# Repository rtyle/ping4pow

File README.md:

# ping4pow

## Motivation

Upon network recovery,
sensitive equipment may need to be rebooted after things have settled.
Some equipment may need to be rebooted to facilitate network recovery.
For many such equipment, power to the device can be cycled to achieve this.
Without automation, this must be done manually.
It would be better with automation that could recognize such conditions and cycle power.

There are commercially available/configurable devices that address this issue.

* [WattBox](https://www.snapav.com/shop/en/snapav/wattbox)
* [Ping Watchdog](https://www.netio-products.com/en/glossary/watchdog-ping-ip-watchdog)

This is a better solution.

Ping4pow can only switch loads that can be safely handled by its relay.
Relay solutions that are embedded in its small footprint will only be able to switch low voltage loads.
However, an external relay solution (like an [iot-power-relay](https://dlidirect.com/products/iot-power-relay))
can be controlled by a GPIO pin for more demanding loads.

## Features

* Small, attractive package
* Display with touchscreen user interface
* Display can be turned off
* User interface can be locked
* Home Assistant integrable but not required for automation
* Wired (ethernet) access for reliable network monitoring
* Powered by [Power-over-Ethernet](https://en.wikipedia.org/wiki/Power_over_Ethernet) (PoE)
* Flexible relay solutions for handling loads
* Galvanically isolated switching of equipment power
* Network health is determined by [ping](https://en.wikipedia.org/wiki/Ping_(networking_utility))ing multiple IP addresses
* Network failure is when all addresses can not be pinged for a while.
* Network recovery may be facilitated by cycling power; otherwise
* Network recovery is when all addresses can be pinged for a while and then power is cycled.
* Email notification of power cycle.

## Architecture

### Hardware

[M5Stack](https://docs.m5stack.com/en/start/intro/intro) products are used to provide a small and attractive hardware solution
that does not require a custom enclosure for switching low voltage loads.
Our stack needs a core with support from a base LAN PoE module.

* [CoreS3-SE](https://docs.m5stack.com/en/core/M5CoreS3%20SE)
* [Base LAN PoE v1.2](https://docs.m5stack.com/en/base/lan_poe_v12)

To support both the core display and the ethernet LAN at the same time, a custom M5-Bus adapter must be used to resolve GPIO pin conflicts. This might be done using an M5Bus bodge-wired Module Proto. Alternately, the PCB of the Module Proto might be swapped out with one that has the bodge baked in (see [adapter](kicad/projects/adapter)).

* [Module Proto](https://docs.m5stack.com/en/module/proto)

To switch the load we will need a relay. M5Stack provides a 4Relay Module. Alternately, the M5-Bus adapter might be expanded to provide a relay using the frame of an M5Stack Module13.2 Proto (see [adapter_relay](kicad/projects/adapter_relay)).

* [Module13.2 4Relay v1.1](https://docs.m5stack.com/en/module/4Relay%20Module%2013.2_V1.1)
* [Module13.2 Proto](https://docs.m5stack.com/en/module/proto13.2)

A Module13.2 Proto might also be used to bodge-wire the M5-Bus adapter and provide external access to the same GPIO pin used by the adapter_relay.
This could be used to drive an external relay for more demanding loads.

### Software

[ESPHome](https://esphome.io/) is used because of its ability to support our chosen hardware and the potential for other choices.
It can be configured in a high level language (YAML) and will only do what you tell it to do.
A configured device can perform all the automations without any external support.
Optionally, such a device can be used by Home Assistant.

## Deployment

### Hardware

The stack should be assembled with the core on top, followed by the relay solution, the adapter solution and finally the PoE base.

#### Module13.2 4Relay v1.1 and Module Proto adapter

This solution uses the Module13.2 4Relay v1.1 and a separate M5-Bus Module Proto based adapter. The adapter can be built from the [adapter](kicad/projects/adapter) kicad project or hand made using its schematic for a reference. If hand made, the disconnected male pins should be clipped and the re-routing of signals made using bodge wires.

<picture>
    <source media="(prefers-color-scheme: dark)" srcset="README/adapter.schematic.dark.png">
    <source media="(prefers-color-scheme: light)" srcset="README/adapter.schematic.light.png">
    
</picture>

Only the first [signal relay](https://www.amazon.com/gp/product/B0CWCTHCFT) in the module will be used.
It will be configured to provide module input power to relay output power in a Normally Closed (NC) fashion.
We want the relay to operate in a NC fashion so that when power is removed from the stack the relay will be closed
(power to the controlled device will be on).

Module input power must be galvanically isolated from the M5-Bus (stack) HPWR and system GND.
**Remove** the jumpers that connect these.

<picture>
    <source media="(prefers-color-scheme: dark)" srcset="README/relay.hpwr.dark.png">
    <source media="(prefers-color-scheme: light)" srcset="README/relay.hpwr.light.png">
    
</picture>

Set the relay jumpers in the "load" configuration.

<picture>
    <source media="(prefers-color-scheme: dark)" srcset="README/relay.load.dark.png">
    <source media="(prefers-color-scheme: light)" srcset="README/relay.load.light.png">
    
</picture>

The relay is hard-wired on the module in a Normally Open (NO) fashion.
That is, the relay output power is connected by PCB trace to the NO pin on the relay.
Cut this trace and add a bodge wire to connect the relay ouput power with the NC pin on the relay.

<picture>
    <source media="(prefers-color-scheme: dark)" srcset="README/relay.dark.png">
    <source media="(prefers-color-scheme: light)" srcset="README/relay.light.png">
    
</picture>

Wire module input power pins to an adapter pigtail that accepts the plug of the power adapter of the controlled device.
Alternately, cut the plug off the power adapter and wire the adapter directly to the 4relay input power plug.
Wire relay power output pins to an adapter pigtail that provides the power plug expected by the controlled device.
Alternately, cut the plug off the power adapter and wire the plug directly to the 4relay output power plug.

#### Module13.2 Proto adapter_relay

This solution uses a Module13.2 Proto frame with the PCB replaced with one built from the [adapter_relay](kicad/projects/adapter_relay) kicad project. There is no need for a separate M5-Bus adapter.

The adapter_relay uses a double-pole double-throw (DPDT) [signal relay](https://na.industrial.panasonic.com/products/relays-contactors/mechanical-signal-relays/lineup/signal-relays/series/119572/model/119942) to switch both conductors of the galvanically isolated DC load. Jumpers must be installed in the normally-closed (NC) positions. The load is passed through the board using standard 5.5mm x 2.1mm DC barrel connections. Openings in the frame of the Module13.2 Proto must be expanded to accomodate the DC jacks. It doesn't matter which jack is used for which plug.

#### Base LAN PoE v1.2

Stack an M5-Bus adapter on top using one of the methods described above.
Power, and supply network access, over the RJ45 ethernet port.

### Software

These instructions are written for a Fedora Linux platform.
Similar steps may be taken for other Linux, MacOS or Windows platforms.

Get the source from this repository by the appropriate method:

    git clone https://github.com/rtyle/ping4pow.git
    git clone git@github.com:rtyle/ping4pow.git

All commands documented here are executed from this directory.

    cd ping4pow

Install python

    sudo dnf install python

Create a python virtual environment for this project.

    python -m venv .venv

Activate the virtual environment every time you want to use ESPHome within this project.

    source .venv/bin/activate

With your virtual environment activated, install ESPHome using pip:

    pip install esphome

Configure the order, address and name of each host to be ping-monitored.
Each is specifed by an address, name pair in an m4 host macro invocation.
Add a third argument for a host that must be power-cycled when all are not pingable for a while;
otherwise, wait for all hosts to be pingable for a while before power-cycling.

    cp config/hosts{.example,}.m4; vi config/hosts.m4

Optionally, configure (smtp) email notification.

    cp config/smtp{.example,}.m4; vi config/smtp.m4

Configure secrets.yaml.

    cp config/secrets{.example,}.yaml; vi config/secrets.yaml

These secrets will be protected by flash encryption on/by the device.

Choose an ESPHome configuration for
M5Stack Module13.2 4Relay hardware (default) or a GPIO relay.

    (cd config; m4 ping4pow.m4 > ping4pow.yaml)
    (cd config; m4 -DGPIO_RELAY ping4pow.m4 > ping4pow.yaml)

The first firmware flash of this ESPHome configuration
must be done with a USB cable between your computer and the M5Stack CoreS3.
**Do not interrupt this first boot!**

    esphome run config/ping4pow.yaml

Upon the first boot after the first flash,
the secondary boot loader will encrypt the content of the flash in place.
Subsequently, only use ESPHome to flash Over The Air (OTA)
as ESPHome flashing by USB will cause the firmware to be unencrypted
which will upset the first stage bootloader to no end:

    [11:31:08.073]invalid header: 0x487325b7
    ...

To recover from this problem, the device must be flashed properly:

    bin=.esphome/build/ping4pow/.pioenvs/ping4pow
    python -m esptool --chip esp32s3 --port /dev/ttyACM0 write-flash --encrypt 0x0 $bin/firmware.factory.bin

Connect by ethernet to a power-over-ethernet capable port and unplug the USB cable.
Connect the switched load to the relay.

## Usage

Each ping target defined (by address & name) and ordered (#) in the `hosts.m4` file will be periodically pinged.
Each will be represented by a

* `ping # (address name)` switch (where # is its order) to enable/disable pinging and summary consideration of the target.
* `ping # able` binary sensor that reflects the pingability of the target.
* `ping # since` sensor that reflects the time elapsed since the last change in pingability.

These target ping sensors will be summarized by a

* `ping none` binary sensor that is true unless an enabled target is pingable.
* `ping all` binary sensor that is true unless an enabled target is not pingable.
* `ping some` binary sensor that is true if "ping none" and "ping all" are false.
* `ping count` sensor that reflects the number of enabled and pingable targets.
* `ping since` sensor that reflects the time elapsed since the last change in target pingability.

The automation provided by ping4pow is implemented as a state machine.
These states are reflected in the user interface as switches.
Only one state/switch can be active/on at a time.
States can be entered through a switch action in the user interface.
These states/switches are:

0. `stop`. When on, the state machine is stopped. Turn off to advance to the next state.
1. wait for `ping none`, then advance to the next state.
2. wait while `ping none`, then advance to the next state; otherwise, the previous state.
3. wait for `ping all`, then advance to the next state.
4. wait while `ping all`, then advance to the next state; otherwise, the previous state.
5. `power cycle`: turn power off, pause, turn power on and then start over.

States 3 and 4 are skipped if there is a host that must be power-cycled when all are not pingable for a while.

If there is 
In addition, ping4pow exposes

* A `power` switch that reflects/controls power to the connected load.
* A `since boot` sensor that reflects the time elapsed since booting the ping4pow device.
* A `since power cycle` sensor that reflects the time elapsed since the power to the load was automatically affected.

All since sensors are in units of seconds.

A web-based user interface at http://ping4pow.local exposes these switches and sensors.

<picture>
    <source media="(prefers-color-scheme: dark)" srcset="README/ping4pow.web.dark.png">
    <source media="(prefers-color-scheme: light)" srcset="README/ping4pow.web.light.png">
    
</picture>

These are also presented locally on the ping4pow device's display.

Under the display are soft buttons on the bezel

* <picture>
        <source media="(prefers-color-scheme: dark)" srcset="README/mdi/chevron-double-left.dark.svg">
        <source media="(prefers-color-scheme: light)" srcset="README/mdi/chevron-double-left.light.svg">
        
    </picture> Decrease display brightness
* <picture>
        <source media="(prefers-color-scheme: dark)" srcset="README/mdi/circle-outline.dark.svg">
        <source media="(prefers-color-scheme: light)" srcset="README/mdi/circle-outline.light.svg">
        
    </picture> Navigate home to state tile
* <picture>
        <source media="(prefers-color-scheme: dark)" srcset="README/mdi/chevron-double-right.dark.svg">
        <source media="(prefers-color-scheme: light)" srcset="README/mdi/chevron-double-right.light.svg">
        
    </picture> Increase display brightness

At the bottom of the display is a user interface lock and tile navigation buttons

* <picture>
        <source media="(prefers-color-scheme: dark)" srcset="README/mdi/arrow-left-bold.dark.svg">
        <source media="(prefers-color-scheme: light)" srcset="README/mdi/arrow-left-bold.light.svg">
        
    </picture> Previous tile in rotation
* <picture>
        <source media="(prefers-color-scheme: dark)" srcset="README/mdi/lock.dark.svg">
        <source media="(prefers-color-scheme: light)" srcset="README/mdi/lock.light.svg">
        
    </picture> User input is locked (<picture>
        <source media="(prefers-color-scheme: dark)" srcset="README/mdi/lock-open.dark.svg">
        <source media="(prefers-color-scheme: light)" srcset="README/mdi/lock-open.light.svg">
        
    </picture> when not)
* <picture>
        <source media="(prefers-color-scheme: dark)" srcset="README/mdi/arrow-right-bold.dark.svg">
        <source media="(prefers-color-scheme: light)" srcset="README/mdi/arrow-right-bold.light.svg">
        
    </picture> Next tile in rotation

The rest of the display is used for the current tile.
Using the next and previous tile controls, one can rotate through them.
The tiles are:

* Splash tile
* State tile
* Since tile
* Target tile (one for each)

### Splash Tile

A ping4pow image is displayed briefly on boot before advancing to the next tile.

### State Tile

The top row of buttons reflect states 1, 2, 3 and 4.

* <picture>
        <source media="(prefers-color-scheme: dark)" srcset="README/mdi/cog-pause.dark.svg">
        <source media="(prefers-color-scheme: light)" srcset="README/mdi/cog-pause.light.svg">
        <picture>
        <source media="(prefers-color-scheme: dark)" srcset="README/mdi/network-off.dark.svg">
        <source media="(prefers-color-scheme: light)" srcset="README/mdi/network-off.light.svg">
        
        </picture>
    </picture> wait for <code>ping none</code>
* <picture>
        <source media="(prefers-color-scheme: dark)" srcset="README/mdi/cog-pause.dark.svg">
        <source media="(prefers-color-scheme: light)" srcset="README/mdi/cog-pause.light.svg">
        <picture>
        <source media="(prefers-color-scheme: dark)" srcset="README/mdi/network-off.dark.svg">
        <source media="(prefers-color-scheme: light)" srcset="README/mdi/network-off.light.svg">
        <picture>
        <source media="(prefers-color-scheme: dark)" srcset="README/mdi/dots-horizontal.dark.svg">
        <source media="(prefers-color-scheme: light)" srcset="README/mdi/dots-horizontal.light.svg">
        
    </picture> wait while <code>ping none</code>
* <picture>
        <source media="(prefers-color-scheme: dark)" srcset="README/mdi/cog-pause.dark.svg">
        <source media="(prefers-color-scheme: light)" srcset="README/mdi/cog-pause.light.svg">
        <picture>
        <source media="(prefers-color-scheme: dark)" srcset="README/mdi/network.dark.svg">
        <source media="(prefers-color-scheme: light)" srcset="README/mdi/network.light.svg">
        
    </picture> wait for <code>ping all</code>
* <picture>
        <source media="(prefers-color-scheme: dark)" srcset="README/mdi/cog-pause.dark.svg">
        <source media="(prefers-color-scheme: light)" srcset="README/mdi/cog-pause.light.svg">
        <picture>
        <source media="(prefers-color-scheme: dark)" srcset="README/mdi/network.dark.svg">
        <source media="(prefers-color-scheme: light)" srcset="README/mdi/network.light.svg">
        <picture>
        <source media="(prefers-color-scheme: dark)" srcset="README/mdi/dots-horizontal.dark.svg">
        <source media="(prefers-color-scheme: light)" srcset="README/mdi/dots-horizontal.light.svg">
        
    </picture> wait while <code>ping all</code>

The middle row of buttons reflect state 0, `power` and state 5

* <picture>
        <source media="(prefers-color-scheme: dark)" srcset="README/mdi/cog.dark.svg">
        <source media="(prefers-color-scheme: light)" srcset="README/mdi/cog.light.svg">
        
    </picture> <code>stop</code> (<picture>
        <source media="(prefers-color-scheme: dark)" srcset="README/mdi/cog-stop.dark.svg">
        <source media="(prefers-color-scheme: light)" srcset="README/mdi/cog-stop.light.svg">
        
    </picture> when stopped)
* <picture>
        <source media="(prefers-color-scheme: dark)" srcset="README/mdi/power.dark.svg">
        <source media="(prefers-color-scheme: light)" srcset="README/mdi/power.light.svg">
        
    </picture> <code>power</code>
* <picture>
        <source media="(prefers-color-scheme: dark)" srcset="README/mdi/power-cycle.dark.svg">
        <source media="(prefers-color-scheme: light)" srcset="README/mdi/power-cycle.light.svg">
        
    </picture> <code>power cycle</code>

The bottom row reflects the summary ping sensors.
At most, one of these will be on.
The label on the widget reflecting state of the `ping some` binary sensor will reflect the `ping count` sensor value regardless.

* <picture>
        <source media="(prefers-color-scheme: dark)" srcset="README/mdi/network-off.dark.svg">
        <source media="(prefers-color-scheme: light)" srcset="README/mdi/network-off.light.svg">
        
    </picture> <code>ping none</code>
* <picture>
        <source media="(prefers-color-scheme: dark)" srcset="README/mdi/pound.dark.svg">
        <source media="(prefers-color-scheme: light)" srcset="README/mdi/pound.light.svg">
        
    </picture> <code>ping some</code> with <code>ping count</code> (#)
* <picture>
        <source media="(prefers-color-scheme: dark)" srcset="README/mdi/network.dark.svg">
        <source media="(prefers-color-scheme: light)" srcset="README/mdi/network.light.svg">
        
    </picture> <code>ping all</code>

### Since Tile

The three rows of this tile reflect times since an event.
This time is formatted as either "N/A" (if there was never such an event) or the number of days, hours, minutes and seconds (D HH:MM:SS) since the event.

* <picture>
        <source media="(prefers-color-scheme: dark)" srcset="README/mdi/check-network.dark.svg">
        <source media="(prefers-color-scheme: light)" srcset="README/mdi/check-network.light.svg">
        
    </picture> <code>ping since</code>
* <picture>
        <source media="(prefers-color-scheme: dark)" srcset="README/mdi/power-cycle.dark.svg">
        <source media="(prefers-color-scheme: light)" srcset="README/mdi/power-cycle.light.svg">
        
    </picture> <code>since power cycle</code>
* <picture>
        <source media="(prefers-color-scheme: dark)" srcset="README/mdi/arrow-up-bold-circle.dark.svg">
        <source media="(prefers-color-scheme: light)" srcset="README/mdi/arrow-up-bold-circle.light.svg">
        
    </picture> <code>since boot</code>

### Target Tile

There is a target tile for each ping target in `hosts.m4`.

The first row of this tile reflects whether the target is enabled and its pingability.

* <picture>
        <source media="(prefers-color-scheme: dark)" srcset="README/mdi/cog.dark.svg">
        <source media="(prefers-color-scheme: light)" srcset="README/mdi/cog.light.svg">
        
    </picture> <code>ping # (address name)</code> enabled (<picture>
        <source media="(prefers-color-scheme: dark)" srcset="README/mdi/cog-stop.dark.svg">
        <source media="(prefers-color-scheme: light)" srcset="README/mdi/cog-stop.light.svg">
        
    </picture> when not)
* <picture>
        <source media="(prefers-color-scheme: dark)" srcset="README/mdi/network.dark.svg">
        <source media="(prefers-color-scheme: light)" srcset="README/mdi/network.light.svg">
         <code>ping # able</code> (<picture>
        <source media="(prefers-color-scheme: dark)" srcset="README/mdi/network-off.dark.svg">
        <source media="(prefers-color-scheme: light)" srcset="README/mdi/network-off.light.svg">
        
        </picture> when not)
    </picture>

The next two rows are for `ping # since` and for identifying the target by address and name.

* <picture>
        <source media="(prefers-color-scheme: dark)" srcset="README/mdi/check-network.dark.svg">
        <source media="(prefers-color-scheme: light)" srcset="README/mdi/check-network.light.svg">
        
    </picture> <code>ping # since</code>
* <picture>
        <source media="(prefers-color-scheme: dark)" srcset="README/mdi/tag.dark.svg">
        <source media="(prefers-color-scheme: light)" srcset="README/mdi/tag.light.svg">
         <code>address</code> <code>name</code>
    </picture>

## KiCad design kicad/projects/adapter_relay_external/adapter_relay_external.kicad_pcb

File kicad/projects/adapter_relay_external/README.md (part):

# GPIO Relay Protection Circuit - Design Documentation

## Overview

This protection circuit provides robust, fail-safe control of an external [DLI IoT Power Relay](https://dlidirect.com/products/iot-power-relay) from an ESP32-based ping4pow device powered by PoE. The circuit is specifically designed to protect the ping4pow hardware from operator errors, including accidental dead shorts and incorrect DC power supply connections (up to 48V).

## Design Philosophy

The circuit follows a **defense-in-depth** strategy with multiple layers of protection:
1. **Galvanic isolation** - Complete electrical isolation between GPIO and external connections
2. **Current limiting** - Series resistance limits fault currents to safe levels
3. **Overvoltage clamping** - Zener diode clamps excessive voltages
4. **Overcurrent protection** - Dual polyfuses interrupt fault conditions
5. **Backfeed prevention** - Schottky diode blocks reverse current flow

Each protection mechanism is **independently validated** to ensure the circuit survives even if one protection layer fails.

## Circuit Architecture

### Schematic Overview

<picture>
    <source media="(prefers-color-scheme: dark)" srcset="README/schematic.dark.png">
    <source media="(prefers-color-scheme: light)" srcset="README/schematic.light.png">
    
</picture>

### Signal Flow

**Normal Operation (GPIO HIGH):**
1. 5V from PoE supply passes through input polyfuse F1
2. Schottky diode D1 drops ~0.25V (at 1mA), preventing backfeed to 5V rail
3. Series resistor R1 (82Ω) limits current
4. Output polyfuse F2 provides additional overcurrent protection
5. Voltage arrives at DC Jack (+) at ~4.67V
6. GPIO HIGH drives optocoupler U1 LED with 10mA
7. U1 phototransistor conducts, connecting DC Jack (-) to GND
8. Relay circuit completes: DC Jack (+) → Relay → DC Jack (-) → U1 → GND
9. Relay receives ~0.95mA at ~4.67V and activates

**Zener D2 monitoring:**
- Connected across DC Jack (+) and DC Jack (-)
- During normal operation: 4.75V < 5.1V threshold, Zener not conducting
- During fault: Clamps voltage between DC Jack (+) and DC Jack (-) to ~5.6V

## Component Selection and Justification

### F1 - Input Polyfuse (Littelfuse 0603L001/60YR)
**Specification:** 10mA hold / 50mA trip, 60V, 0603 package

**Purpose:** Protects the 5V PoE supply rail from overcurrent faults, particularly dead shorts at the DC jack output.

**Selection Rationale:**
- **Hold current (10mA):** Normal relay current is ~0.95mA, giving 10.5x safety margin
- **Trip current (50mA):** Dead short produces 58mA, exceeding trip threshold by 16%
- **Trip time at 58mA:** Approximately 5-30 seconds
- **Component stress during trip:** R1 dissipates 0.28W (56% of 0.5W rating), all components safe
- **60V rating:** Exceeds maximum expected voltage (48V) with 25% margin
- **Availability:** Minimum trip current available from Littelfuse in required voltage rating

**Why this trip point:** This was the lowest trip current available in 0603 SMD package with adequate voltage rating. The 50mA trip provides reliable protection for dead shorts (58mA) while not tripping during normal operation (0.95mA).

### F2 - Output Polyfuse (Littelfuse 0603L008YR)
**Specification:** 80mA hold / 200mA trip, 60V, 0603 package

**Purpose:** Protects R1 and D2 from excessive current when external overvoltage sources (wall adapters) are connected to the DC jack.

**Selection Rationale:**
- **Hold current (80mA):** Provides 84x margin over normal relay current
- **Trip current (200mA):** At 48V fault, current reaches 517mA (2.6x trip threshold), causing F2 to trip within 1-2 seconds
- **Why this matters:** Limits duration that D2 must dissipate 2.9W and R1 must handle 22W pulse
- **Placement:** On output side (after R1) to specifically protect against external fault sources

### D1 - Schottky Diode (OnSemi SS16T3G)
**Specification:** 60V, 1A, Vf ~0.25V @ 1mA, SMA package

**Purpose:** Prevents reverse current (backfeed) into the 5V PoE supply when external voltages are applied to DC jack.

**Selection Rationale:**
- **60V rating:** Handles worst-case differential (48V input minus 5.6V Zener clamp = 42.4V) with 43% margin
- **Schottky advantage:** Forward voltage only 0.25V at 1mA vs 0.7V for standard diode
  - Maximizes voltage to relay: 4.67V with Schottky vs 4.25V with standard diode
  - Lower voltage drop critical for relay operation at minimum current
- **Measured Vf:** At 0.95mA operating current, Vf ≈ 0.25V (verified empirically)
  - Much lower than 0.4-0.5V specified at higher currents (100mA+)
  - Datasheet curves don't extend below 100mA, actual measurement essential

**Backfeed protection:** When external voltage >5.25V appears at DC jack, D1 becomes reverse-biased and blocks current from reaching 5V rail, protecting all PoE-powered devices.

### D2 - Zener Diode (MCC SMBJ5338B-TP)
**Specification:** 5.1V nominal, 5W continuous, SMB package

**Purpose:** Clamps voltage across DC jack output (between + and -), protecting the relay and providing current path to trip F2 during overvoltage faults.

**Selection Rationale:**
- **5.1V nominal voltage:** 
  - Normal operation: 4.75V < 5.1V threshold, Zener doesn't conduct
  - Under load: Clamps at ~5.6V
  - Chosen as closest available voltage to operating point (4.75V) while maintaining margin
- **Why not 5.0V:** Not available in 5W SMB package from major distributors
- **Why not 6.2V:** Would clamp at ~6.8V, allowing higher voltage to reach relay and increasing Zener power dissipation (3.2W vs 2.9W at 48V fault)
- **5W power rating critical for 48V fault:**
  - Power dissipation: 5.6V × 517mA = 2.9W
  - Utilization: 58% of 5W rating (42% safety margin)
  - Duration: 1-2 seconds until F2 trips
- **Thermal management:** SMB package with ≥100mm² copper pour per pin (top + bottom layers, thermal vias) provides adequate heat dissipation

**Connection:** Zener is connected directly across DC jack output (cathode to DC+, anode to DC-), NOT between DC+ and GND. This allows it to clamp voltage regardless of optocoupler state.

### R1 - Series Resistor (Panasonic ERJ-P14F82R0U)
**Specification:** 82Ω, 0.5W, 1% tolerance, 1210 package

**Purpose:** Primary current-limiting element protecting against faults. Limits current during shorts and overvoltage conditions.

**Selection Rationale - Balancing Three Requirements:**

**1. Normal Operation:**
- Voltage drop: 0.95mA × 82Ω = 78mV
- Relay receives: 4.75V - 0.078V = 4.67V ✓
- Minimal impact on relay voltage

**2. Dead Short Protection:**
- Current: 4.75V / 82Ω = 58mA
- Exceeds F1 trip threshold (50mA) by 16% ✓
- Reliable protection

**3. Overvoltage Protection:**
- At 48V: (48V - 5.6V) / 82Ω = 517mA
- Zener power: 2.9W (within 5W rating) ✓
- F2 trips at 200mA threshold ✓

**Alternatives Rejected:**
- **100Ω:** Dead short only 47mA < 50mA trip threshold (unreliable)
- **68Ω:** Higher Zener stress (624mA, 3.5W), less margin
- **120Ω+:** Dead short well below F1 trip, no protection

**Power Rating Analysis:**
- **Normal:** 0.074mW (negligible)
- **Dead short:** (58mA)² × 82Ω = 276mW for 5-30s (55% of rating, safe)
- **48V fault:** (517mA)² × 82Ω = 21.9W for 1-2s (pulse loading)

**Pulse Power Survival:**
- 1210 package thermal mass: ~0.5 J/°C
- Energy absorbed: 21.9W × 1.5s = 33J
- Temperature rise: ~60-80°C
- Peak temperature: 40°C (warm) + 80°C = 120°C
- Within limits: Thick-film resistors rated to 155°C
- Status: Survives pulse ✓

### R2 - GPIO Current Limiter (Panasonic ERJ-S08J331V)
**Specification:** 330Ω, 1/4W, 5% tolerance, 1206 package

**Purpose:** Limits current from ESP32 GPIO to optocoupler LED.

**Selection Rationale:**
- **Value:** At GPIO HIGH (3.3V): I = 3.3V / 330Ω = 10mA
- **GPIO protection:** ESP32 can source 20-40mA; 10mA is 25-50% of capability (safe)
- **Opto LED requirement:** 10mA provides adequate CTR for phototransistor saturation
- **Power:** (10mA)² × 330Ω = 33mW (13% of 0.25W rating)

### U1 - Optocoupler (Lite-On LTV-817S)
**Specification:** CTR ≥50%, 5000V isolation, SOP-4 package

**Purpose:** Provides complete galvanic isolation between ESP32 GPIO and DC jack. This is the **primary protection** preventing any external voltage from reaching the GPIO.

**Selection Rationale:**
- **5000V isolation:** Even if high voltage appears at DC jack, isolation barrier prevents any voltage from reaching GPIO
- **Protection philosophy:** This isolation protects ESP32 even if all other protection mechanisms fail
- **CTR ≥50%:** 10mA LED current produces ≥5mA collector current
- **Switching function:** Phototransistor connects DC Jack (-) to GND when activated
  - GPIO HIGH → LED on → Phototransistor conducts → DC- connected to GND → Relay operates
  - GPIO LOW → LED off → Phototransistor off → DC- floating → Relay inactive

**Why opto instead of transistor:** Direct transistor switching would not provide isolation. Any fault voltage could damage GPIO through transistor junctions.

## Expected Load Characterization

### DLI IoT Power Relay Input Specifications

**From manufacturer FAQ:**
- Trigger current: ~0.2mA
- Input type: "Constant current"
- Voltage range: 3.3-48VDC (DC polarity sensitive)
- Control type: Opto-isolated input

### Empirical Characterization Results

The relay's electrical characteristics were measured using bench power supply through 100Ω series resistor:

| Supply Voltage | Voltage Across 100Ω | Relay Current | Relay Status |
|----------------|---------------------|---------------|--------------|
| 2.0V | 26mV | 0.26mA | OFF |
| 2.1V | 29mV | 0.29mA | **ON (just triggered)** |
| 3.0V | 71mV | 0.71mA | ON |
| 4.0V | 88mV | 0.88mA | ON |
| 4.7V | 95.3mV | 0.95mA | ON |
| 4.8V | 96.3mV | 0.96mA | ON |
| 5.0V | 99mV | 0.99mA | ON |

### Key Findings

**1. Trigger Threshold: 0.29mA**
- Measured trigger: 0.29mA at 2.1V supply
- Manufacturer spec: ~0.2mA
- Close agreement: 0.29mA is 45% above minimum spec (good margin in relay itself)

**2. Current Increases with Voltage (Not Constant)**
- From 2.1V to 5.0V: Current increases from 0.29mA to 0.99mA (3.4x increase)
- This contradicts manufacturer's "constant current" claim
- Likely: Current regulation begins at higher voltages (>5V), not measured
- Behavior in measured range: Current increases nonlinearly, suggesting active regulation

**3. Not a Simple Resistor**
- If simple LED + resistor, internal resistance would be constant
- Calculated "apparent resistance" varies: 2.4kΩ to 7kΩ depending on operating point
- Conclusion: Relay input has current-limiting/regulation circuitry

**4. Rate of Current Increase Slows at Higher Voltages**
- 2.1V to 3.0V (+0.9V): Current increases 0.42mA
- 3.0V to 4.0V (+1.0V): Current increases 0.17mA  
- 4.0V to 5.0V (+1.0V): Current increases 0.11mA
- Shows increasing regulation effect at higher voltages

### Circuit Operating Point

**Normal operation analysis:**
```
5.00V  PoE supply
-0.00V  F1 (negligible resistance when not tripped)
-0.25V  D1 Schottky forward voltage at 1mA
---------
4.75V  Available at junction after D1

-0.08V  R1 voltage drop (82Ω × 0.95mA)
---------
4.67V  At DC Jack (+)
```

**From measured I-V curve:**
- At 4.67V relay input: Current ≈ 0.95mA (interpolated between 4.7V and 4.8V measurements)
- This provides **4.75x margin** above 0.2mA trigger threshold
- Relay operates reliably with substantial headroom

**Operating Margins:**
- Current margin: 0.95mA / 0.2mA = **4.75x above trigger threshold**
- Voltage margin: 4.67V / 2.1V = **2.2x above minimum trigger voltage**
- Both provide comfortable safety margins for reliable operation

## Protection Against Unexpected Loads

**CRITICAL NOTE:** In all fault scenarios below, the **relay is NOT connected**. When a user plugs in a wall adapter, short circuit, or reversed polarity, they have replaced the relay with the fault source. The fault analysis does not consider relay behavior.

### Scenario 1: Dead Short at DC Jack

**Fault condition:** User accidentally shorts DC Jack (+) to DC Jack (-) with wire, tool, or conductive object.

**Circuit behavior:**

**Current path:**
```
5V PoE → F1 → D1 (0.25V drop) → R1 (82Ω) → DC Jack (+) → SHORT → DC Jack (-) → Opto ON → GND
```

For current to flow in a dead short, it needs a path back to GND. **This requires the Opto to be ON**.

1. **Initial state:** 58mA flows through R1, then through short to GND
2. **F1 heating:** At 58mA (1.16x trip current), F1 heats and trips in 5-30 seconds
3. **Component stress during fault:**
   - R1: (58mA)² × 82Ω = 276mW (55% of 0.5W rating) ✓ Safe
   - D1: 58mA × 0.3V ≈ 17mW ✓ Safe
   - F1: Self-heating to trigger trip (by design)
4. **After F1 trips:** Current drops to ~4mA (through F1's high-resistance state), circuit protected
5. **Recovery:** Remove short, F1 cools and resets automatically

### Scenario 2: 12V Wall Adapter

**Fault condition:** User plugs 12V DC wall adapter into DC jack instead of relay.

**Critical understanding:** The **wall adapter provides both (+) and (-) terminals**, creating a complete circuit through the wall adapter itself.

**Circuit behavior:**

**Current path:**
```
12V wall wart (+) terminal
    ↓
DC Jack (+)
    ↓
F2 → R1 (82Ω)
    ↓
D2 Zener (connected between DC+ and DC-)
    ↓
DC Jack (-)
    ↓
12V wall wart (-) terminal
```

**The wall adapter completes the circuit** regardless of GPIO/optocoupler state. The Zener sees 12V across it and clamps.

**Analysis:**
1. **Zener clamping:** D2 conducts in breakdown mode, clamping voltage across DC jack to ~5.6V
2. **Current:** (12V - 5.6V) / 82Ω = **78mA**
3. **F2 status:** 78mA < 200mA trip threshold → F2 does NOT trip
4. **Power dissipation:**
   - Zener: 5.6V × 78mA = **437mW** (9% of 5W rating) ✓ Safe
   - R1: (78mA)² × 82Ω = **499mW** (approaching 0.5W rating, but safe) ✓

**Steady state:**
- Circuit can remain in this condition indefinitely
- Zener safely dissipates 437mW with proper thermal management
- R1 near its rating but within limits
- No component damage
- User eventually notices relay doesn't work (voltage too low)

**5V rail protection:**
- D1 Schottky is reverse-biased: Cathode at 5.6V (clamped), Anode at 5V
- Reverse voltage: Only 0.6V across D1
- No current flows back to 5V PoE rail ✓

**Note:** GPIO state is irrelevant - wall adapter provides complete circuit path through itself.

### Scenario 3: 24V Wall Adapter

**Fault condition:** 24V DC wall adapter connected to DC jack.

**Analysis:**
1. **Zener clamping:** D2 clamps to ~5.6V across DC jack
2. **Current:** (24V - 5.6V) / 82Ω = **224mA**
3. **F2 trips:** 224mA exceeds 200mA trip threshold by 12%
4. **Trip time:** 2-5 seconds at this overcurrent level
5. **Component stress during fault:**
   - Zener: 5.6V × 224mA = **1.25W** for 2-5 seconds (25% of 5W rating) ✓
   - R1: (224mA)² × 82Ω = **4.1W** pulse (thermal mass absorbs energy) ✓
   - Both survive the brief pulse until F2 trips

**After F2 trips:**
- F2 resistance → ~1kΩ (high impedance state)
- Current drops: 18.4V / 1082Ω = 17mA
- Zener power: 5.6V × 17mA = 95mW (negligible)
- Circuit protected

**Recovery:** Remove adapter, F2 cools and automatically resets (30-60 seconds)

**5V rail:** Protected by D1, no backfeed (0.6V reverse bias) ✓

### Scenario 4: 48V Power Supply (Worst Case)

**Fault condition:** 48V DC supply applied to DC jack (maximum voltage relay is rated for, also common telecom/PoE voltage).

**This is the design's worst-case scenario** - highest current, maximum component stress.

**Analysis:**

**Phase 1: Initial fault (0 to 1-2 seconds)**
1. **Zener clamping:** D2 conducts heavily, clamping to ~5.6V
2. **Fault current:** (48V - 5.6V) / 82Ω = **517mA**
3. **Power dissipation:**
   - Zener: 5.6V × 517mA = **2.9W** (58% of 5W rating)
   - R1: (517mA)² × 82Ω = **21.9W** pulse loading

**Phase 2: F2 trips (1-2 seconds)**
- Current (517mA) is 2.6x the 200mA trip threshold
- F2 trips **rapidly** due to severe overcurrent
- Trip time: 1-2 seconds

**Component survival analysis:**

**D2 (Zener) - Critical component:**
- Rated: 5W continuous, SMB package
- Actual: 2.9W for 1-2 seconds
- Margin: 42% below rating
- Thermal design: 100mm² copper per pin (top + bottom) + thermal vias
- Temperature rise: ~40-60°C above ambient
- Peak temp: ~85-105°C (well below 150°C rating)
- **Status: SURVIVES** ✓

**R1 (82Ω) - Critical component:**
- Rated: 0.5W continuous (1210 package)
- Actual: 21.9W for 1-2 seconds (43.8x overload!)
- Thermal mass: ~0.5 J/°C for 1210 resistor body
- Energy absorbed: 21.9W × 1.5s = 33J
- Temperature rise: 33J / 0.5J/°C = 66°C
- Starting temp: ~40°C (warm from normal operation)
- Peak temp: 40°C + 66°C = ~106°C
- Absolute max: Thick-film resistors rated to 155°C
- Margin: 49°C below absolute maximum
- **Status: SURVIVES** ✓

**Phase 3: After F2 trips**
- F2 → high resistance (~1kΩ)
- Current: 42.4V / 1082Ω = 39mA
- Zener: 5.6V × 39mA = 218mW (negligible)
- R1: (39mA)² × 82Ω = 125mW (25% of rating)
- Circuit protected, can remain indefinitely

**5V rail protection:**
- D1 reverse voltage: 5.6V - 5.0V = 0.6V (trivial)
- No backfeed ✓

**Why this is worst case:**
- Highest fault current (517mA)
- Maximum Zener power (2.9W)
- Maximum R1 pulse power (22W)
- If circuit survives this, it survives any lower voltage

**Design validation:** All components remain within absolute maximum ratings with margin. No damage occurs even in this extreme fault condition.

### Scenario 5: Reverse Polarity

**Fault condition:** User plugs DC supply with reversed polarity (negative to center pin, positive to sleeve).

**Voltage distribution:**
- DC Jack (+) [center pin]: Connected to negative terminal (e.g., -12V if 12V adapter)
- DC Jack (-) [sleeve]: Connected to positive terminal (e.g., +12V)

**Circuit behavior:**

**Zener orientation with reversed polarity:**
- D2 cathode (normally toward positive): Now sees -12V
- D2 anode (normally toward DC-): Now sees +12V
- Zener is forward-biased (conducts like regular diode)
- Forward voltage: ~0.7V typical for Zener in forward conduction

**Current path:**
```
12V (+) at DC Jack (-) → Zener (forward, 0.7V drop) → Zener cathode → R1 → F2 → DC Jack (+) at -12V
```

But this creates issues - where does current flow to complete circuit?

**Analysis:**
- The Zener conducts forward with ~0.7V drop
- This clamps voltage across relay connection points to ~0.7V
- Current is limited by total resistance and forward Zener characteristic
- Current: (12V - 0.7V) / ~82Ω ≈ 138mA through Zener in forward mode

**Result:**
- Zener forward conduction limits voltage to ~0.7V across jack
- Zener dissipates: 0.7V × 138mA ≈ 97mW (safe)
- No damage to circuit
- User notices relay doesn't work

**Note:** Reverse polarity protection is a beneficial side-effect of the Zener's forward conduction characteristic, not a primary design goal. The low forward voltage prevents damage.

## Design Trade-offs and Alternatives Considered

### R1 Value Selection: Why 82Ω?

The 82Ω value balances three competing requirements:

**Requirement 1: Adequate relay voltage (Normal operation)**
- Too high: Excessive voltage drop, insufficient voltage for relay
- 82Ω drops only 78mV at 0.95mA
- Relay receives 4.67V (adequate for 0.95mA operation)

**Requirement 2: Dead short protection**
- Too high: Insufficient current to trip F1
- 82Ω produces 58mA short current
- Exceeds F1's 50mA trip by 16% (reliable)

**Requirement 3: Overvoltage protection**
- Too low: Excessive Zener and resistor stress
- 82Ω limits 48V fault to 517mA
- Zener: 2.9W (within 5W rating)
- R1: 22W pulse (survives)

**Alternatives evaluated:**

| R1 Value | Normal V Drop | Relay V | Short I | F1 Trip? | 48V I | Zener W | R1 Pulse W | Verdict |
|----------|---------------|---------|---------|----------|-------|---------|------------|---------|
| 68Ω | 65mV | 4.69V | 70mA | Yes ✓ | 624mA | 3.5W | 27W | Higher stress |
| **82Ω** | **78mV** | **4.67V** | **58mA** | **Yes ✓** | **517mA** | **2.9W** | **22W** | **Optimal** |
| 100Ω | 95mV | 4.66V | 47mA | **No ✗** | 424mA | 2.4W | 18W | No protection |
| 120Ω | 114mV | 4.64V | 40mA | **No ✗** | 354mA | 2.0W | 15W | No protection |

**Conclusion:** 82Ω is the optimal value providing reliable protection while maintaining adequate relay voltage and acceptable component stress.

### F1 Trip Current: Why 10mA/50mA?

**Ideal trip current:** Should be as low as possible while:
- Not tripping during normal operation (0.95mA)
- Reliably tripping on dead short (58mA)

**Availability constraint:**
- Searched Mouser and Digikey for SMD polyfuses in 0603 package
- Minimum available trip current: **50mA** (Littelfuse 0603L series)
- Lower trip currents (20mA, 30mA) not available in required voltage rating (60V) and package size

**Why 10mA hold / 50mA trip:**
- Hold: 10.5x margin over normal current (very safe)
- Trip: Dead short (58mA) exceeds by 16% (adequate margin)
- This was the **lowest available** option meeting all requirements

**Trade-off accepted:** Would prefer 30mA trip for faster response, but 50mA trip still provides reliable protection with acceptable trip time (5-30 seconds).

### Zener Voltage: Why 5.1V?

**Requirement:** Zener must not conduct during normal operation but must clamp during faults.

**Normal operating voltage at Zener location:**
- After Schottky D1: 4.75V
- At DC Jack: 4.67V
- Zener sees voltage between DC Jack (+) and DC Jack (-): ~4.67V when relay operating

**Voltage selection criteria:**
- Must be above 4.67V (normal operation) to avoid conducting
- Should be as low as practical to minimize clamping voltage and Zener power during faults
- Must be available in 5W rating, SMB package

**Options evaluated:**

| Zener Voltage | Normal V | Conducts? | Clamp V | 48V Fault I | Zener Power | Availability |
|---------------|----------|-----------|---------|-------------|-------------|--------------|
| 5.0V | 4.67V | Marginal | ~5.5V | 519mA | 2.85W | Not available in 5W SMB |
| **5.1V** | **4.67V** | **No ✓** | **~5.6V** | **517mA** | **2.9W** | **Available ✓** |
| 5.6V | 4.67V | No ✓ | ~6.2V | 510mA | 3.16W | Available |
| 6.2V | 4.67V | No ✓ | ~6.8V | 503mA | 3.42W | Available |

**Selection: 5.1V nominal (SMBJ5338B-TP)**
- Adequate margin above normal voltage (4.67V < 5.1V threshold)
- Clamps at lowest voltage (~5.6V under 517mA load)
- Minimizes Zener power dissipation (2.9W vs 3.4W for 6.2V)
- Available in required 5W rating and SMB package from multiple distributors

**Why not 5.0V:** Not available in 5W SMB package from Mouser/Digikey. 5.1V was closest available option.

**Clamping voltage under load:** Zener nominal voltage is measured at low test current. Under heavy load (517mA at 48V fault), actual clamping voltage is approximately 0.5V higher than nominal, hence 5.1V nominal clamps at ~5.6V.

### R1 Power Rating: 0.5W vs 1W

**Normal operation:** 0.074mW (trivial - any rating adequate)

**Dead short:** 276mW for 5-30 seconds
- 0.5W rating: 55% utilization (adequate with margin)
- 1W rating: 28% utilization (overkill)

**48V fault:** 21.9W for 1-2 seconds (pulse loading)
- 0.5W (1210 package): Thermal mass ~0.5 J/°C, survives 33J pulse with 66°C rise ✓
- 1W (2512 package): Thermal mass ~1.0 J/°C, survives 33J pulse with 33°C rise (better margin)

**Package size:**
- 1210 (0.5W): 3.2mm × 2.5mm
- 2512 (1W): 6.4mm × 3.2mm (2.5x larger area)

**Decision: 0.5W (1210 package)**
- Adequate for all operating conditions including worst-case 48V fault
- Smaller footprint (important for compact PCB)
- Lower cost
- Thermal analysis confirms survival of 22W pulse for 1-2 seconds
- If concerned: 1W (2512) provides additional thermal margin but not required

**Trade-off:** Accepted tighter thermal margin on 48V fault in exchange for smaller size and lower cost. Analysis confirms safety with margin.

### Optocoupler: Why Not Direct Transistor Switching?

**Alternative considered:** Use NPN transistor directly (GPIO → base, DC- to collector, GND to emitter)

**Advantages of transistor:**
- Lower cost (~$0.05 vs ~$0.25 for optocoupler)
- Lower voltage drop (Vce(sat) ~0.2V vs ~0.3V for optocoupler)
- Simpler

**Critical disadvantage:**
- **No galvanic isolation**
- If fault voltage appears at DC jack, transistor provides path to GPIO through base-collector or base-emitter junctions
- Even with base resistor, high voltage can break down transistor junctions
- GPIO damage possible

**Optocoupler advantage:**
- 5000V isolation barrier - **complete protection** even if all other protection fails
- This is the **primary defense** - if Zener fails open, F2 doesn't trip, etc., the optocoupler still protects GPIO
- Cost difference ($0.20) is trivial compared to protecting $20-30 ESP32 module

**Decision:** Optocoupler is non-negotiable for robust protection. The isolation is the primary reason the GPIO is safe.

## PCB Layout Guidelines

### Trace Width Recommendations (1 oz copper)

**High-current fault paths (20-30 mil):**
- Net **DC+** (DC Jack + to F2): **30 mil**
- Net **F2** (between F2 and R1): **30 mil**
- Net **Z** (R1 to Zener cathode/DC Jack +): **30 mil**
- Net **DC-** (DC Jack - to Zener anode/optocoupler collector): **30 mil**

These traces must handle up to 517mA during 48V fault for 1-2 seconds.

**Normal current paths (10 mil):**
- **+5V** (PoE to F1): **10 mil**
- **F1** (between F1 and D1): **10 mil**
- **D1 output** (D1 cathode to R1): **10 mil**
- **GPIO** (GPIO to R2): **10 mil**
- **LED** (R2 to U1 pin 1): **10 mil**

**Ground:**
- Use **copper pour** on bottom layer (flood fill)
- Connect all ground points (U1 emitter, component grounds, GPIO ground)
- Do not route ground as traces

### Thermal Management for D2 (Zener)

**Critical:** D2 must dissipate up to 2.9W during 48V fault for 1-2 seconds.

**SMB Package Requirements:**
- Minimum copper area: 100mm² total (50mm² per pin)
- Both top and bottom layers
- Thermal vias connecting layers

**Top Layer (Component Side):**
1. **Create copper pour on net Z** (cathode pad):
   - Area: ≥50mm² (approximately 7mm × 7mm)
   - Shape: Rectangular or rounded rectangle around pad
   - Connection: **Direct/solid** (no thermal relief spokes)

2. **Create copper pour on net DC-** (anode pad):
   - Area: ≥50mm² (approximately 7mm × 7mm)
   - Shape: Rectangular or rounded rectangle around pad
   - Connection: **Direct/solid** (no thermal relief spokes)

**Bottom Layer:**
1. Mirror the top layer pours:
   - Net Z: ≥50mm² copper pour
   - Net DC-: ≥50mm² copper pour

2. Connect to main copper pours/traces for these nets

**Thermal Vias:**
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
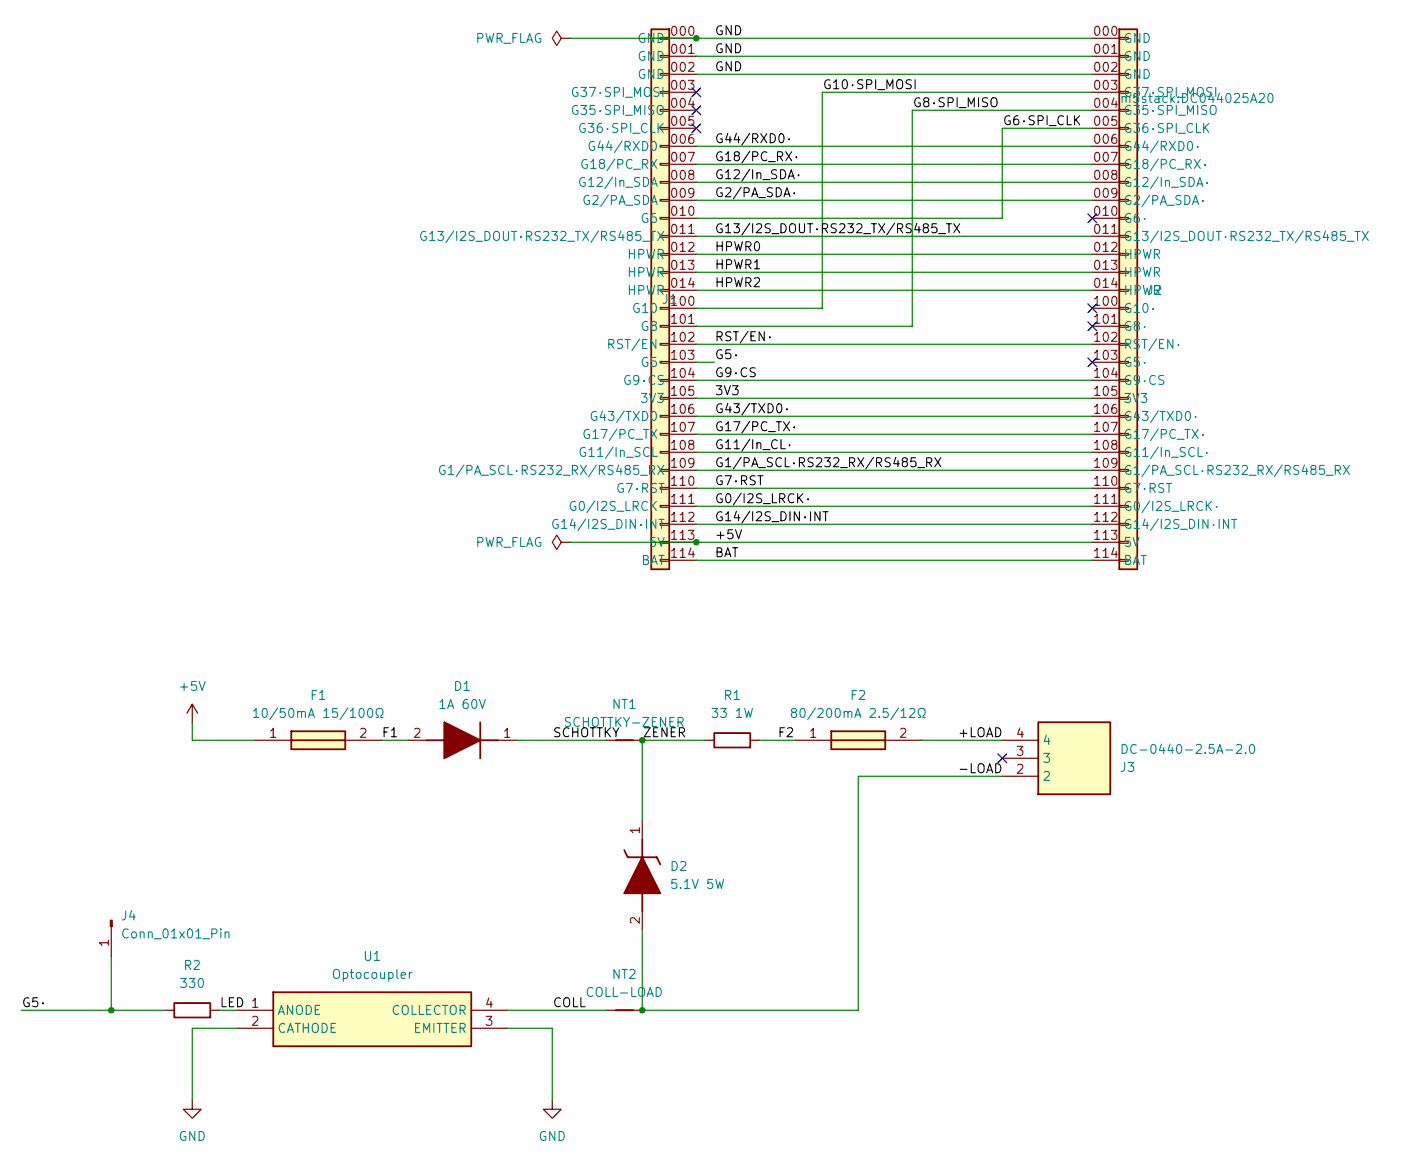
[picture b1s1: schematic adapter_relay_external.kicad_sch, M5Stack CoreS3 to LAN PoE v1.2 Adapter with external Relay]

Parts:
D1: 1A 60V; DIOM5226X220N; Mouser Part Number 863-SS16T3G
D2: 5.1V 5W; DIOM5336X262N; Mouser Part Number 833-SMBJ5338B-TP
F1: 10/50mA 15/100Ω; FUSC1608X100N; Mouser Part Number 576-0603L001/60YR
F2: 80/200mA 2.5/12Ω; FUSC1608X100N; Mouser Part Number 576-0603L008YR
J1: M5Stack A117 PinHeader; PinHeader_2x15_P2.54mm_Vertical_SMD_M5Stack_A001; Mouser Part Number 170-A117
J2: M5Stack A117 PinSocket; PinSocket_2x15_P2.54mm_Vertical_SMD_M5Stack_A001; Mouser Part Number 170-A117
J3: DC-0440-2.5A-2.0; DC044025A20; Manufacturer_Part_Number DC-0440-2.5A-2.0
J4: Conn_01x01_Pin; PinHeader_1x01_P1.00mm_Vertical
NT1: SCHOTTKY-ZENER; NetTie-2_SMD_Pad0.5mm
NT2: COLL-LOAD; NetTie-2_SMD_Pad0.5mm
R1: 33 1W; R_1210_3225Metric; Mouser Part Number 755-ESR25JZPJ330
R2: 330; R_1206_3216Metric; Mouser Part Number 667-ERJ-S08J331V
U1: Optocoupler; SOP254P1016X460-4N; Mouser Part Number 859-LTV-817S

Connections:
+5V: F1.1, J1.113 (5V), J2.113 (5V)
/3V3: J1.105 (3V3), J2.105 (3V3)
/+LOAD: F2.2, J3.4
/-LOAD: D2.2 (A), J3.2, NT2.2
/BAT: J1.114 (BAT), J2.114 (BAT)
/COLL: NT2.1, U1.4 (COLLECTOR)
/F1: D1.2 (A), F1.2
/F2: F2.1, R1.2
/G0/I2S_LRCK·: J1.111 (G0/I2S_LRCK·), J2.111 (G0/I2S_LRCK·)
/G1/PA_SCL·RS232_RX/RS485_RX: J1.109 (G1/PA_SCL·RS232_RX/RS485_RX), J2.109 (G1/PA_SCL·RS232_RX/RS485_RX)
/G2/PA_SDA·: J1.009 (G2/PA_SDA·), J2.009 (G2/PA_SDA·)
/G5·: J1.103 (G5·), J4.1, R2.1
/G6·SPI_CLK: J1.010 (G6·), J2.005 (G36·SPI_CLK)
/G7·RST: J1.110 (G7·RST), J2.110 (G7·RST)
/G8·SPI_MISO: J1.101 (G8·), J2.004 (G35·SPI_MISO)
/G9·CS: J1.104 (G9·CS), J2.104 (G9·CS)
/G10·SPI_MOSI: J1.100 (G10·), J2.003 (G37·SPI_MOSI)
/G11/In_CL·: J1.108 (G11/In_SCL·), J2.108 (G11/In_SCL·)
/G12/In_SDA·: J1.008 (G12/In_SDA·), J2.008 (G12/In_SDA·)
/G13/I2S_DOUT·RS232_TX/RS485_TX: J1.011 (G13/I2S_DOUT·RS232_TX/RS485_TX), J2.011 (G13/I2S_DOUT·RS232_TX/RS485_TX)
/G14/I2S_DIN·INT: J1.112 (G14/I2S_DIN·INT), J2.112 (G14/I2S_DIN·INT)
/G17/PC_TX·: J1.107 (G17/PC_TX·), J2.107 (G17/PC_TX·)
/G18/PC_RX·: J1.007 (G18/PC_RX·), J2.007 (G18/PC_RX·)
/G43/TXD0·: J1.106 (G43/TXD0·), J2.106 (G43/TXD0·)
/G44/RXD0·: J1.006 (G44/RXD0·), J2.006 (G44/RXD0·)
/HPWR0: J1.012 (HPWR), J2.012 (HPWR)
/HPWR1: J1.013 (HPWR), J2.013 (HPWR)
/HPWR2: J1.014 (HPWR), J2.014 (HPWR)
/LED: R2.2, U1.1 (ANODE)
/RST/EN·: J1.102 (RST/EN·), J2.102 (RST/EN·)
/SCHOTTKY: D1.1 (K), NT1.1
/ZENER: D2.1 (K), NT1.2, R1.1
GND: J1.000 (GND), J1.001 (GND), J1.002 (GND), J2.000 (GND), J2.001 (GND), J2.002 (GND), U1.2 (CATHODE), U1.3 (EMITTER)

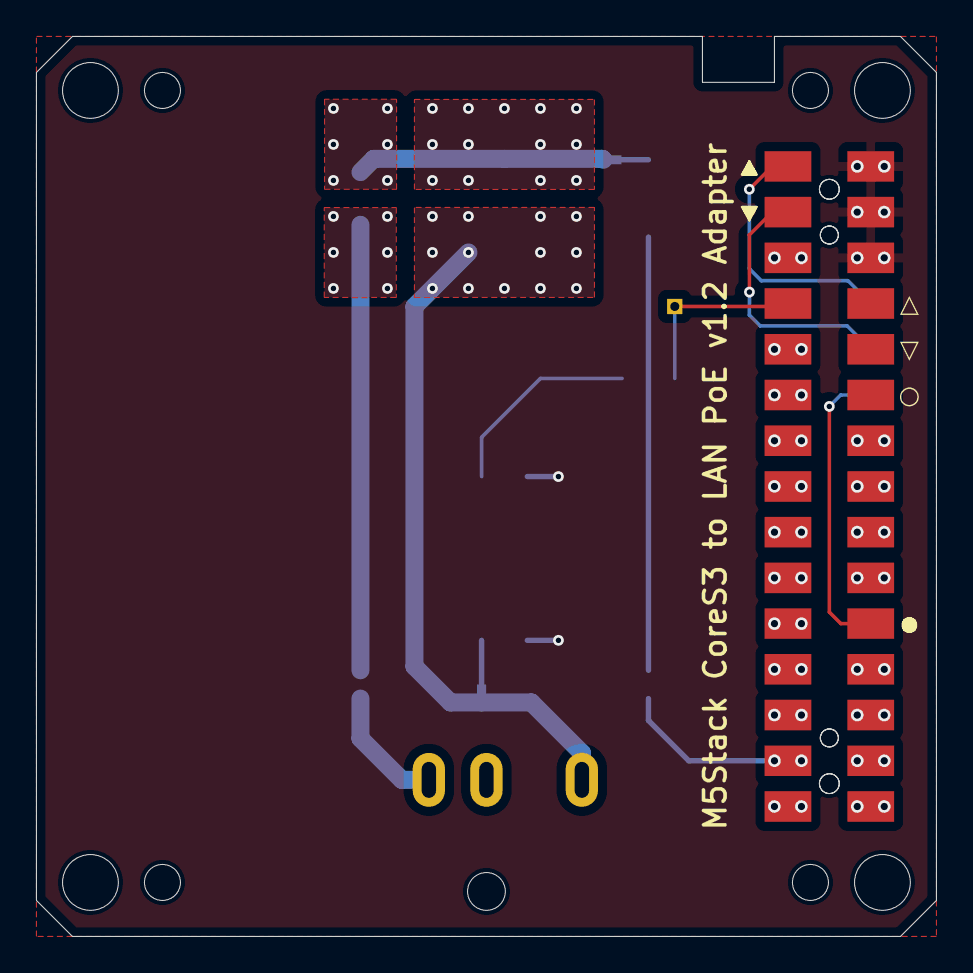
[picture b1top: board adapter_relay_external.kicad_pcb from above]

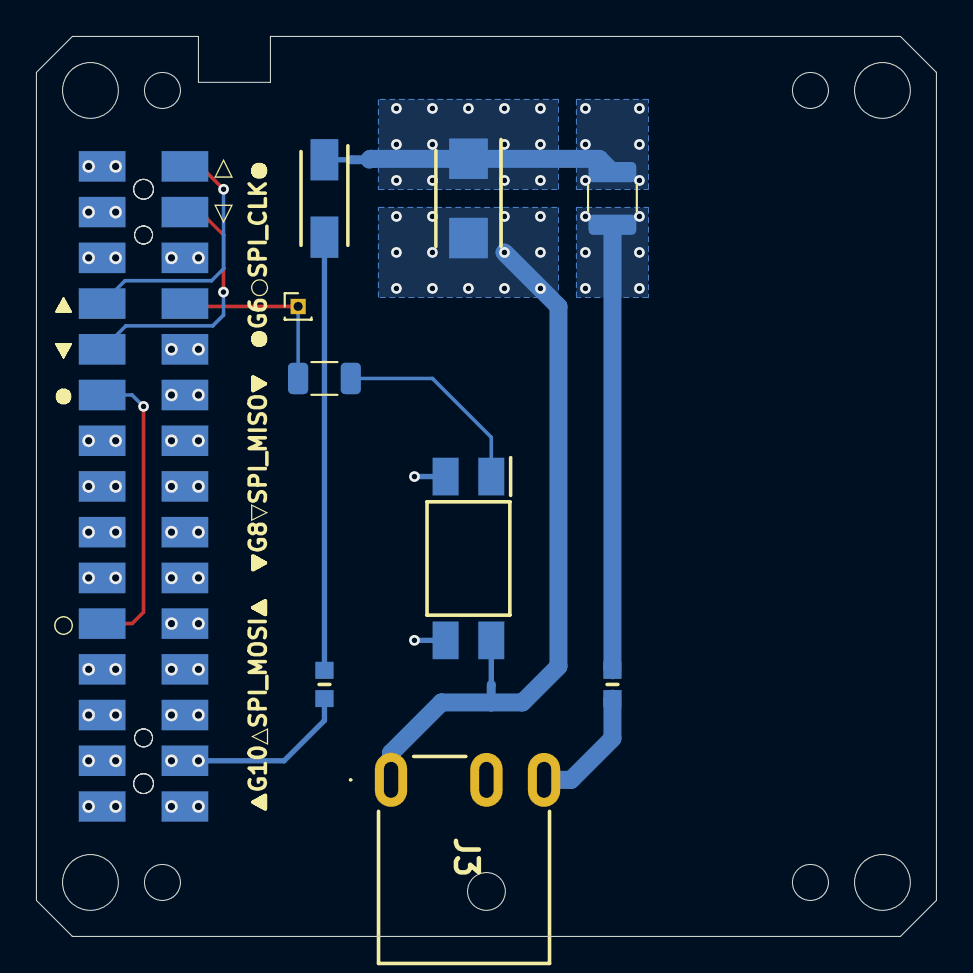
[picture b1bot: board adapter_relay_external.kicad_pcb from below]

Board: 2 copper layers, 50.0 x 50.0 mm, 13 parts (12 on the bottom side), 33 nets.

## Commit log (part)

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2025-07-24 pingandpow → ping4pow
2025-07-25 M5Burner
2025-07-25 build, install and run
2025-07-26 Update README.md
    requirements
2025-07-26 requirements
2025-07-26 Module Proto
2025-07-27 proto images
2025-07-27 relay image
2025-07-27 relay images
2025-09-14 mdi:pound
2025-09-14 fix README.md MDI icons in light and dark modes
2025-09-14 include gpio_relay configuration in README
2025-09-14 Update README.md
    describe load constraints, workarounds
2025-09-14 Update README.md
    code highlights
2025-09-14 highlight code
2025-09-14 hosts.example.m4
2025-09-14 ping4pow.home.png
2025-09-14 ping4pow.web.{dark,light}.png
2025-09-14 ping4pow.web.{light,dark}.png ping4pow.home.png
2025-09-16 _m5cores3_touchscreen bezel cleanup
2025-09-16 ping interval 15s, timeout 2s, steady 60s
2025-09-16 light and dark pngs
2025-09-16 README.md uses <picture> to select source based on light/dark mode
2025-09-16 rm docs/.gitkeep
2025-09-17 _m5cores3_touchscreen cleanup
2025-09-17 whitespace
2025-09-18 gpio relay restore mode off
2025-09-23 add wait for ping none state
2025-09-24 relay.{dark,light}.png
2025-09-25 cpu frequency 240Mhz
2025-09-25 web_server version 3
2025-09-25 hosts.example.m4 match README
2025-09-25 sdkconfg lwip resource limits
2025-10-07 ping since change
2025-10-07 LOGI ping change
2025-10-08 m4 -DNAME=name -DHOSTS=hosts -DGPIO_RELAY
2025-10-09 extend since sensor schema with unit_of_measurement, etc.
2025-10-09 add a text_sensor for each _since sensor to _format::duration(x)
2025-10-09 config/.gitignore
2025-10-09 add a text_sensor for _power_since to format::duration(x)
2025-10-09 _format::duration(x) yields "NA" on NaN (like web UI for sensor)
2025-10-10 add optional text and label to _since and update them with formatted state
2025-10-10 _since depends on _format
2025-10-10 _since owns/creates its optional text_sensor
2025-10-10 -DLOGGER_LEVEL, GPIO_RELAY restore_mode ALWAYS_ON
2025-10-11 ping target address must be resolvable at config time
2025-10-11 target address and name are separate lvgl widgets
2025-10-12 requires_esp_idf
2025-10-22 MULTI_CONF
2025-10-22 smtp
2025-10-22 Update README with email notification details
    Added information about email notifications for power cycles and SMTP configuration.
2025-10-22 screenshots
2025-10-23 smtp cleanup
2025-10-23 ping4pow.png
2025-10-23 reorder relay solutions
2025-10-23 mv docs README
2025-10-23 rm ping4pow.home.png
2025-10-23 README.md resources in README/
2025-10-23 README.md -> README/ping4pow.png
2025-10-24 explicit reinterpret_cast
2025-10-27 adapter_relay_external
2025-10-27 Revise voltage thresholds and current flow details
    Updated voltage thresholds and current flow descriptions in the README.
2025-10-27 Update README by removing revision history and license
    Removed the revision history and license sections from the README, while retaining key information about the design status and key takeaway.
2025-10-27 adapter_relay_external/README
2025-10-27 adapter_relay_external/README/schematic.{dark,light}.png
2025-10-28 Replace 'opto-isolator' with 'optocoupler' in README
2025-10-28 Rename 'Opto-Isolator' to 'Optocoupler' in README
2025-10-28 concat.hpp #pragma once
2025-10-28 .gitignore kicad project backups
2025-10-28 uppercase CRLF
2025-10-28 raii.hpp already included by smtp.h
2025-10-28 _smtp logs stack headroom during run_
2025-10-29 Update README for clarity on M5-Bus adapter
2025-11-04 tune dc jack footprint and pcb placement
2025-11-05 simplify raii.hpp to use std::unique_ptr with no move constructors
2025-11-06 smtp raii cleanup
2025-11-06 delay mbed_ssl_context construction until needed
2025-11-07 std::optional<std::string> send_
2025-11-07 comment
2025-11-07 move dc jack, tune R1 spec, add gpio pin
2025-11-09 rename raii::Raii to raii::Resource. raii::Resource is a/the resource type
2025-11-09 #pragma once
2025-11-14 handle CRLF terminated lines correctly
2025-11-14 removed undefined behavior from std::isdigit calls
2025-11-14 prefer brace initialization
2025-11-15 address -Wall issues
2025-11-15 fix ESP_LOGE formatting error
2025-11-15 fix InputStream initialization order
2025-11-17 compile our components with strict GCC warnings and resolve them
2025-11-17 inline primitive constants
2025-11-17 minor cleanup
2025-11-17 smtp getline as a simple free function
2025-11-17 prefer unnamed namespaces over statics
2025-11-17 cleanup
2025-11-20 use C++20 concepts in raii
2025-11-21 implementation in detail namespace
2025-11-21 optional task_name and task_priority config of _smtp
2025-11-21 __* ids renamed to *_widget_
2025-11-21 _* ids renamed to *_
2025-11-22 _* components renamed to *_
2025-11-22 _smtp_send macro handles smtp use and not
2025-11-22 *.h -> *.hpp
2025-11-22 N/A -> NA
2025-11-22 constexpr auto LOG
2025-11-22 auto
2025-11-23 <id> -> <id>_
2025-11-24 password: !secret smtp_password
2025-11-24 .gitignore /secrets.yaml
2025-11-24 key: !secret NAME-api-key
2025-11-24 password: !secret NAME-ota-password
2025-11-25 brace initialization
2025-11-26 const everything
2025-11-29 clang-tidy, prefer references over pointers, task run class method via lambda
2025-11-29 -Werror, clang-tidy fixes, SmtpReply tuning
2025-11-30 prefer std::{unique_ptr,make_unique} over new and delete
2025-12-01 freertos queue with raii cleanup
2025-12-01 clang-tidy
2025-12-05 cleanup ping callback lambdas
2025-12-06 use asio esp-idf component for ping_
2025-12-06 ping.io -> ping.io_
2025-12-10 ping uses asio async without exceptions in esphome thread
2025-12-11 get/check error code from socket open call
2025-12-11 create queue at smtp component construction time instead of waiting for setup
2025-12-11 resolve collisions with multiple components using same asio_detail_throw_exception_.hpp
2025-12-11 ordering
2025-12-12 ping_ uses shared asio_ esphome component to manage espressif/asio config
2025-12-13 cleanup before co_return
2025-12-15 ping_ loop poll_one
2025-12-16 use asio for smtp component
2025-12-16 ESP_LOGE -> ESP_LOGD, Reply{-1}
2025-12-17 std::round(seconds)
2025-12-19 tightly scope resolver
2025-12-19 add_idf_component espressif/asio fix(asio): memory leaks over ssl::stream lifetime
2025-12-19 trim some fat
2025-12-20 ping4pow splash tile
2025-12-20 ping4pow tile widget in last column
2025-12-20 better ping4pow splash image
2025-12-21 ping4pow.png gold glow behind cog
2025-12-22 encrypt flash to protect secrets
2025-12-23 comments
2025-12-23 log of first boot after encrypt settings made
2025-12-23 secrets.example.yaml
2025-12-23 Enhance README with configuration and flashing details
    Updated instructions for configuring secrets and flashing firmware.
2025-12-23 mv secrets.example.yaml config/
2025-12-23 README.vscode.txt
2025-12-24 const
2025-12-25 splash ping4pow image on_boot
2025-12-25 Document Splash tile in README
    Added description for Splash tile in README.
2026-01-29 pair buttons occupying same grid locations in obj containers
2026-02-03 configure psram component
2026-02-03 #pragma GCC diagnostic ignored "-Wconversion"
2026-02-12 espressif/asio new release with memory leak bugfix
2026-02-14 8192 stack size, treat powered hosts differently
2026-02-17 revert
2026-02-17 Update README for clarity on network recovery
    Clarify network recovery conditions and power cycling process in the README.
2026-02-17 last button in row 2 reflects state 5
2026-05-08 #pragma GCC diagnostic ignored "-Wold-style-cast" FOR #include "esphome/core/component.h"
2026-05-09 fix smtp.hpp play signature
2026-05-14 remove unused smtp task_name and task_priority
2026-06-03 work around esphome deprecations
